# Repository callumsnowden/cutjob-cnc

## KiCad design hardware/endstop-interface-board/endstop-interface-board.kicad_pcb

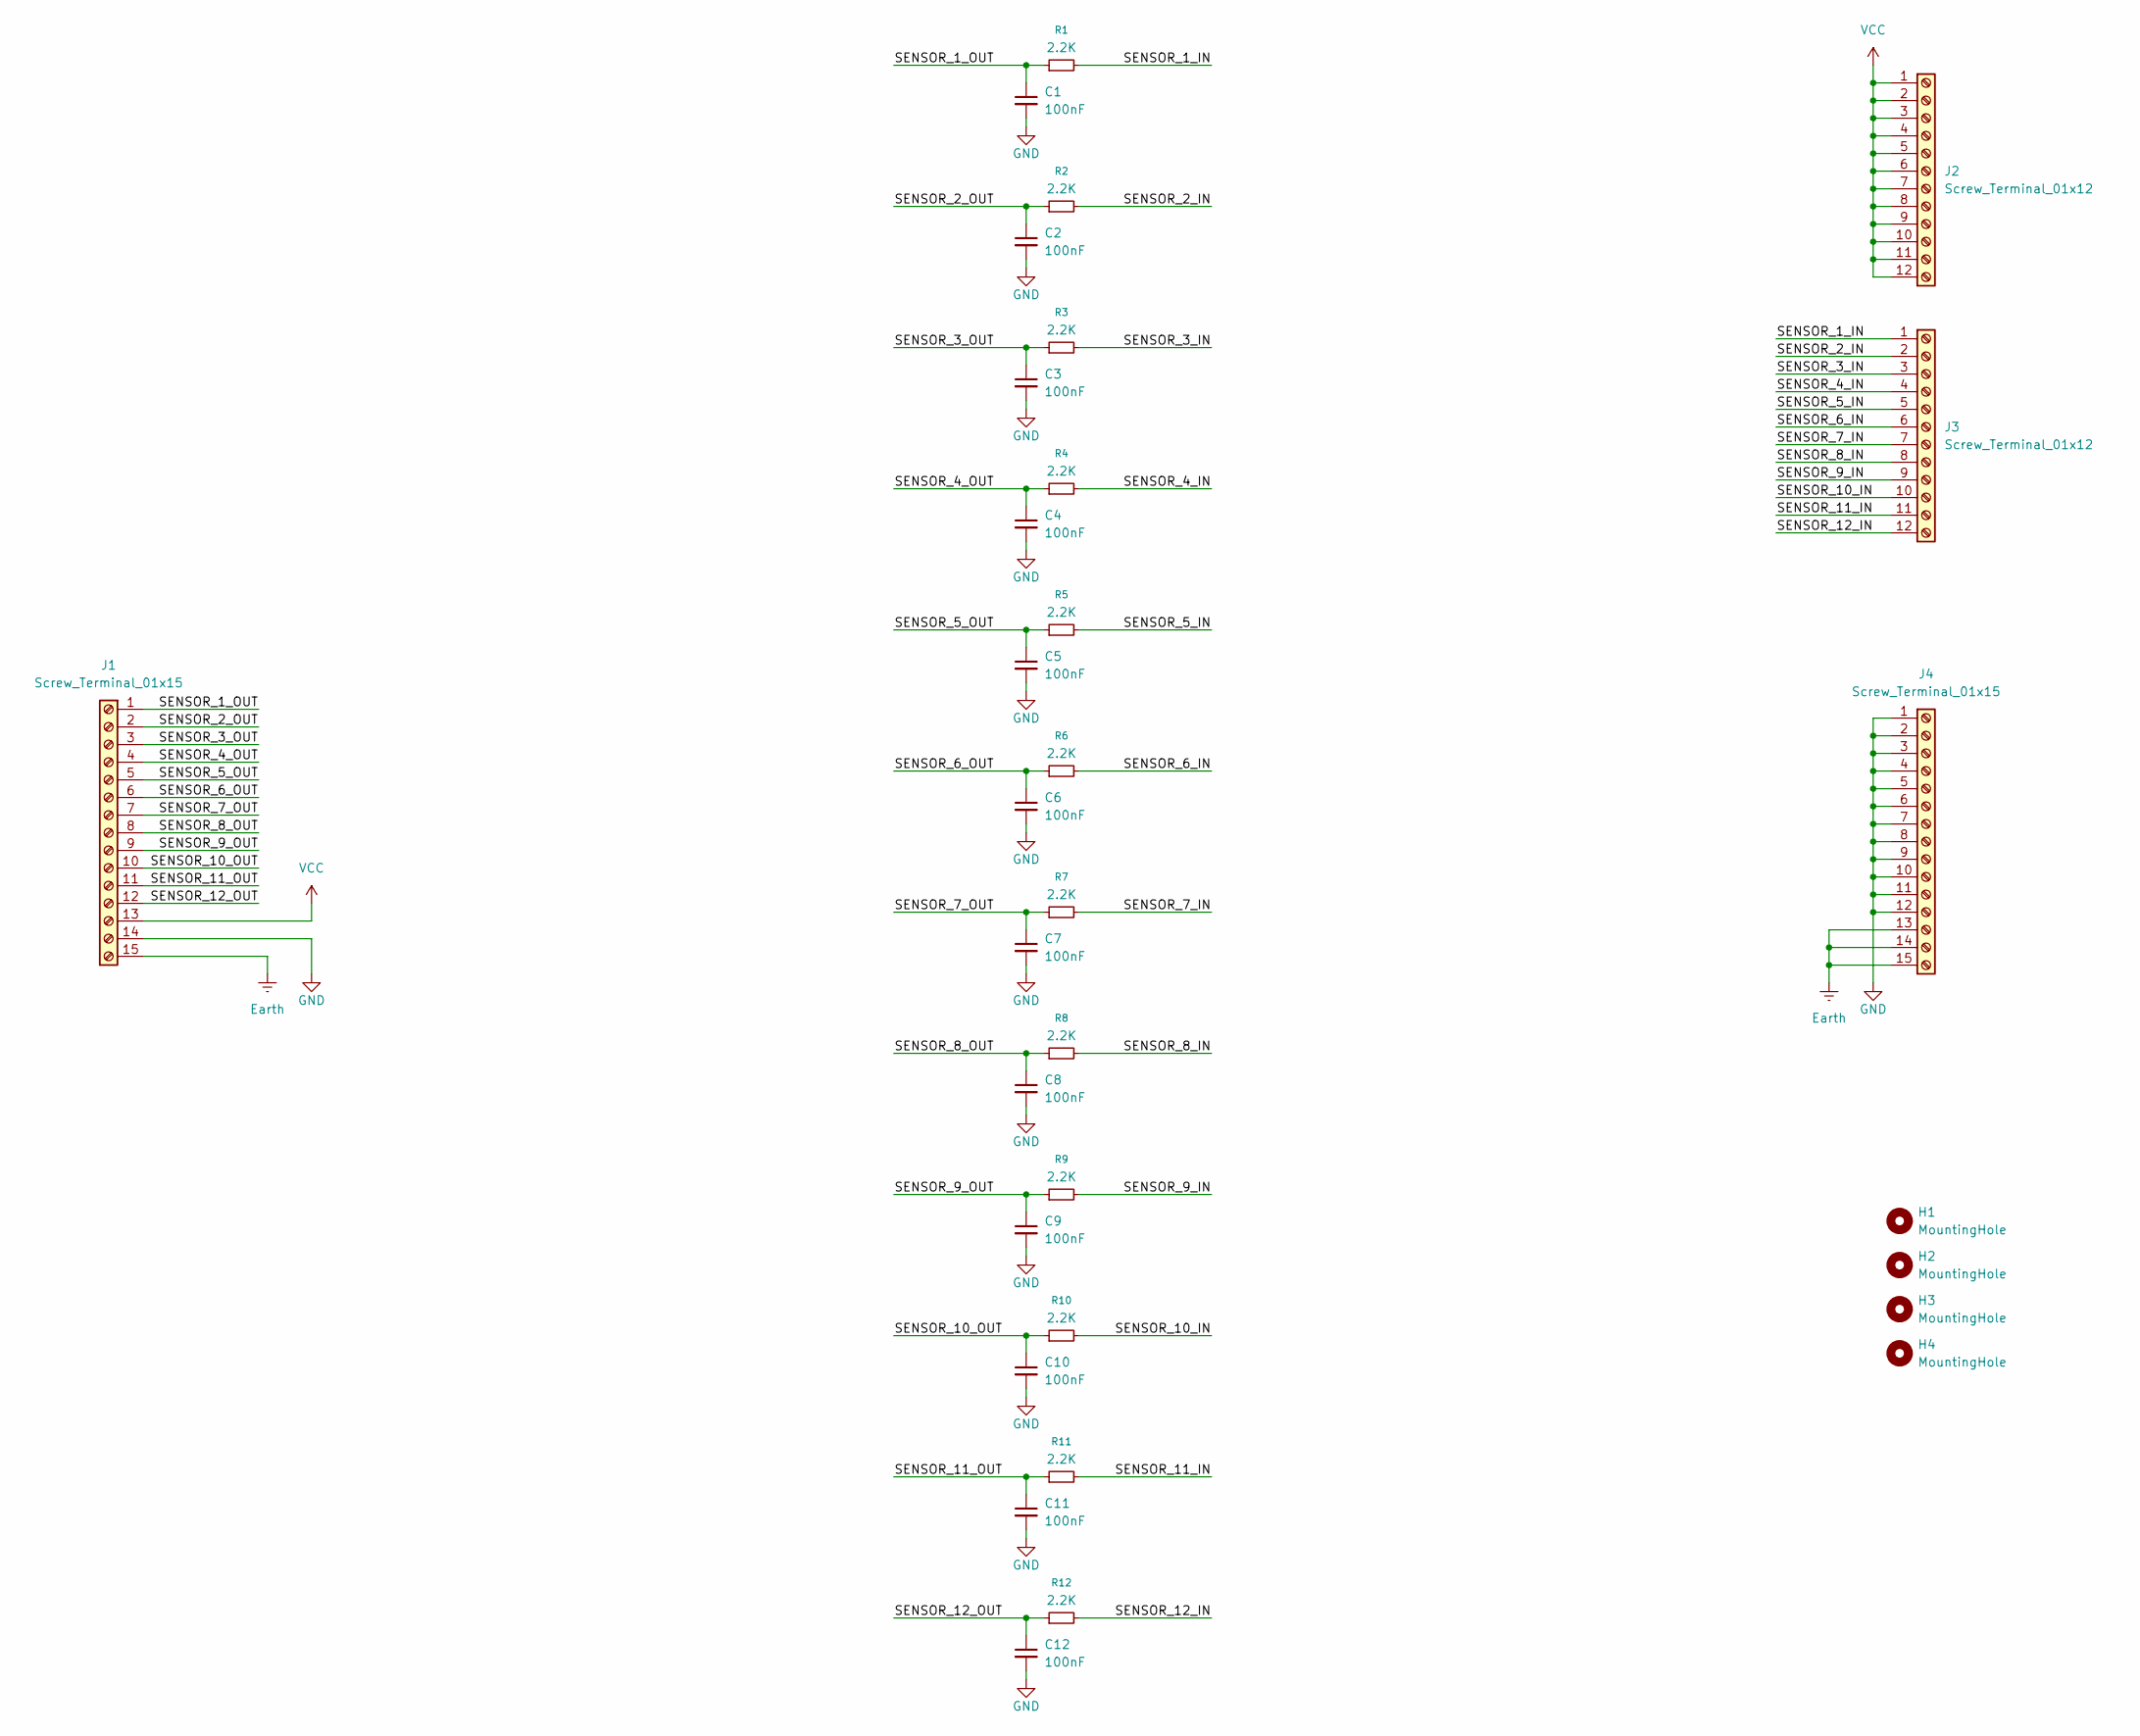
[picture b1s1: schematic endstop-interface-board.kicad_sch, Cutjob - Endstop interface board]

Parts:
C1, C2, C3, C4, C5, C6, C7, C8, C9, C10, C11, C12: 100nF; C_0603_1608Metric
H1, H2, H3, H4: MountingHole; MountingHole_3.2mm_M3
J1, J4: Screw_Terminal_01x15; TerminalBlock_CUI_TB007-508-15_1x15_P5.08mm_Horizontal
J2, J3: Screw_Terminal_01x12; TerminalBlock_CUI_TB007-508-12_1x12_P5.08mm_Horizontal
R1, R2, R3, R4, R5, R6, R7, R8, R9, R10, R11, R12: 2.2K; R_0603_1608Metric

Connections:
/SENSOR_1_IN: J3.1, R1.2
/SENSOR_1_OUT: C1.1, J1.1, R1.1
/SENSOR_2_IN: J3.2, R2.2
/SENSOR_2_OUT: C2.1, J1.2, R2.1
/SENSOR_3_IN: J3.3, R3.2
/SENSOR_3_OUT: C3.1, J1.3, R3.1
/SENSOR_4_IN: J3.4, R4.2
/SENSOR_4_OUT: C4.1, J1.4, R4.1
/SENSOR_5_IN: J3.5, R5.2
/SENSOR_5_OUT: C5.1, J1.5, R5.1
/SENSOR_6_IN: J3.6, R6.2
/SENSOR_6_OUT: C6.1, J1.6, R6.1
/SENSOR_7_IN: J3.7, R7.2
/SENSOR_7_OUT: C7.1, J1.7, R7.1
/SENSOR_8_IN: J3.8, R8.2
/SENSOR_8_OUT: C8.1, J1.8, R8.1
/SENSOR_9_IN: J3.9, R9.2
/SENSOR_9_OUT: C9.1, J1.9, R9.1
/SENSOR_10_IN: J3.10, R10.2
/SENSOR_10_OUT: C10.1, J1.10, R10.1
/SENSOR_11_IN: J3.11, R11.2
/SENSOR_11_OUT: C11.1, J1.11, R11.1
/SENSOR_12_IN: J3.12, R12.2
/SENSOR_12_OUT: C12.1, J1.12, R12.1
Earth: J1.15, J4.13, J4.14, J4.15
GND: C1.2, C2.2, C3.2, C4.2, C5.2, C6.2, C7.2, C8.2, C9.2, C10.2, C11.2, C12.2, J1.14, J4.1, J4.2, J4.3, J4.4, J4.5, J4.6, J4.7, J4.8, J4.9, J4.10, J4.11, J4.12
VCC: J1.13, J2.1, J2.2, J2.3, J2.4, J2.5, J2.6, J2.7, J2.8, J2.9, J2.10, J2.11, J2.12

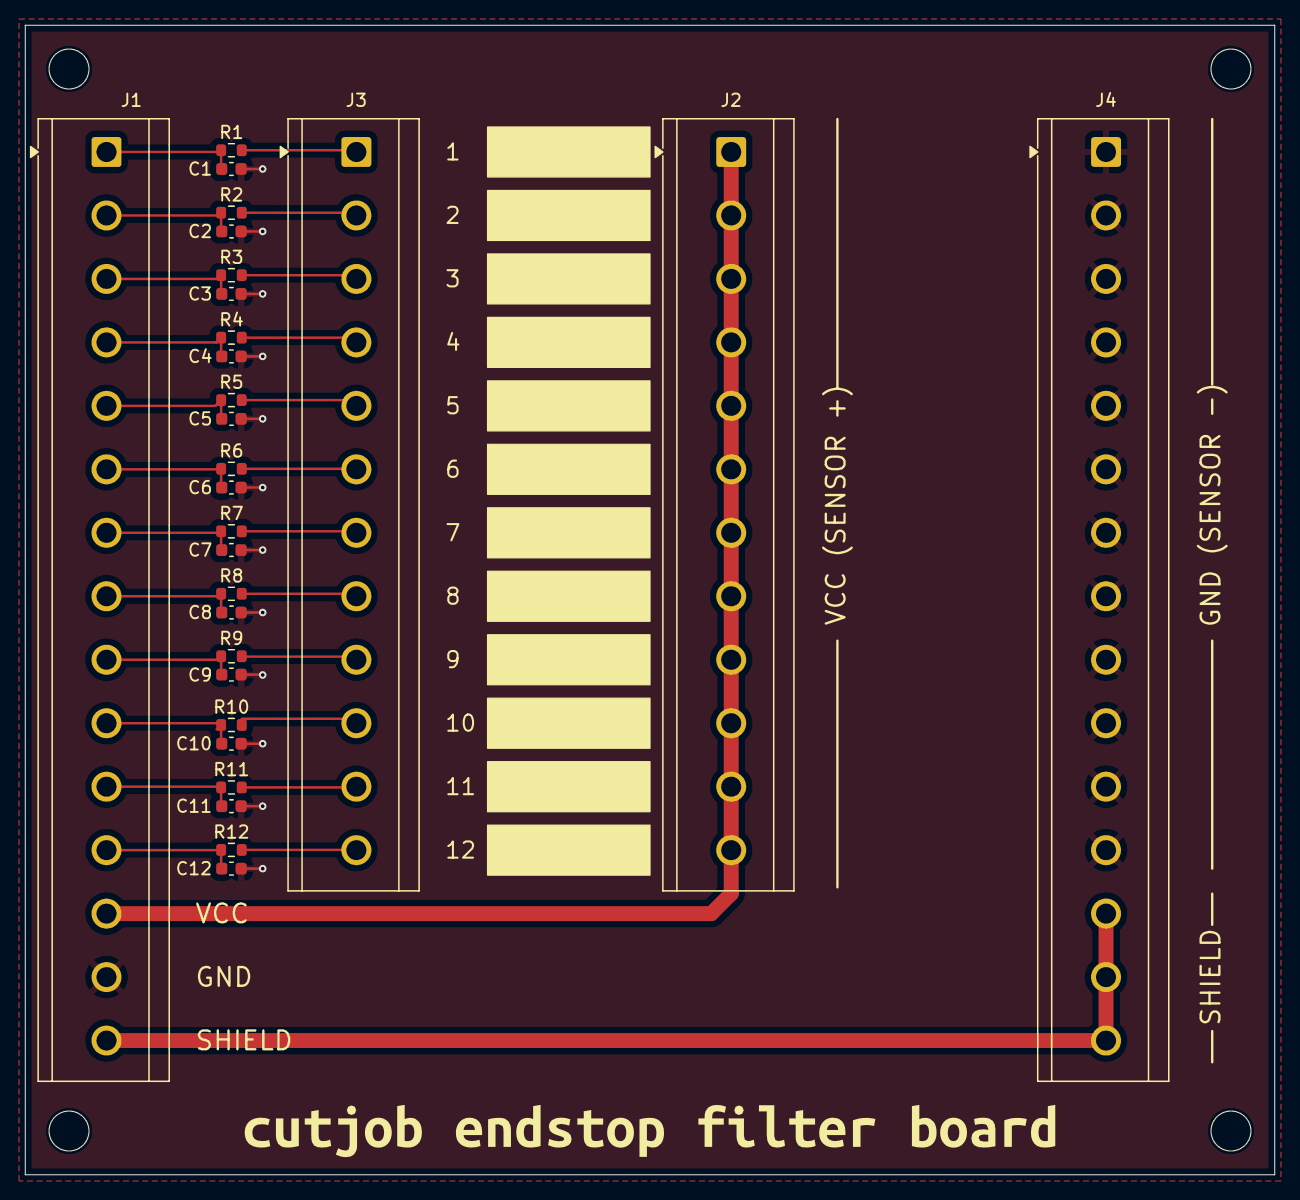
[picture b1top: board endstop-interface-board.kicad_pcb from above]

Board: 2 copper layers, 100.0 x 92.0 mm, 33 parts (0 on the bottom side), 27 nets.

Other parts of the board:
kibuzzard-695BA6A9: G***; kibuzzard-695BA6A9

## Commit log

2025-12-22 Start work on endstop board
2026-01-05 Add completed endstop filter board
2026-01-30 Add STEP files
